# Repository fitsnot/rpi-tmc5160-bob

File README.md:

# rpi-tmc5160-bob
Quick and dirty stepper motor controller based on Raspberry Pi Pico and Trinamic TMC5160-BOB [PCB] [ARDUINO]
The goal is to have either a potentiometer or magentic encoder as rotary input that controls the speed of a large stepper motor. SPI and the integrated motion controller of the Trinamic TMC5160 is used to reduce computational load on the MCU as low as possible.

## Code
The TMC5160_Arduino library by tommag https://github.com/tommag/TMC5160_Arduino is used.

TODO:
- [x] Initial test with RPI and TMC5160-BOB
- [ ] Integrate AS5600 as rotary encoder
- [ ] Tune for utilised MOSFETS

## PCB
FIrst draft uses Raspberry Pi Pico and either a TMC5160-BOB ("Breakout board") or a corresponding SilentStepstick. A AS5600 can be used as a rotary encoder via I2C protocol.

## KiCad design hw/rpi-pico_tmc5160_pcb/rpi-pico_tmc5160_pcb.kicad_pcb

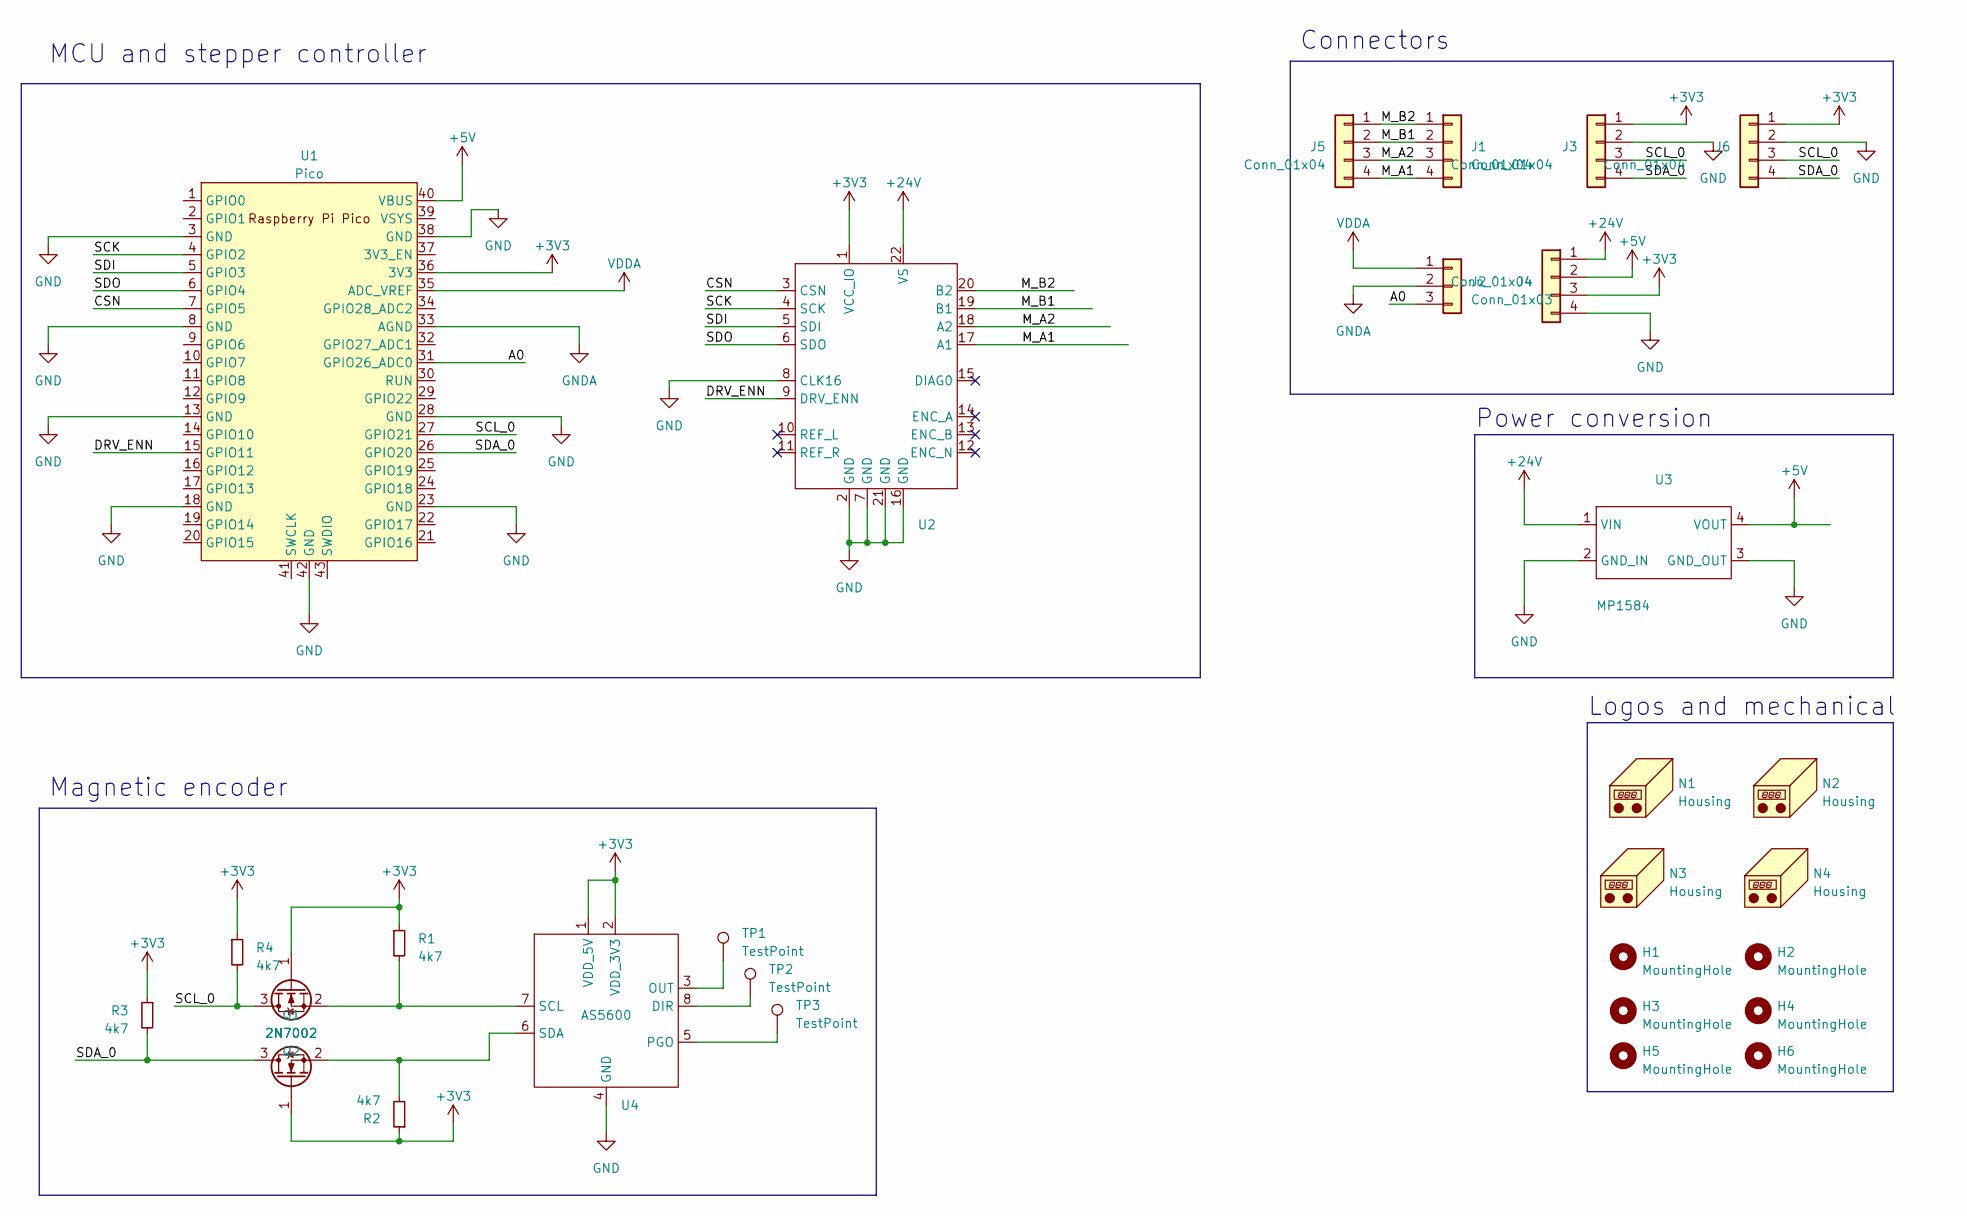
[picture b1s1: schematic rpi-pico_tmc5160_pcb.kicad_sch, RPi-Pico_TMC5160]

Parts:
H1, H2, H3, H4, H5, H6: MountingHole; MountingHole_3.2mm_M3_ISO7380
J1, J4: Conn_01x04; Wago_734-134_1x04_P3.50mm_Vertical; LCSC C557656
J2: Conn_01x03; JST_XH_B3B-XH-A_1x03_P2.50mm_Vertical; LCSC C144394
J3, J5, J6: Conn_01x04; JST_XH_B4B-XH-A_1x04_P2.50mm_Vertical; LCSC C144395
N1, N2, N3, N4: Housing; Mousebite
Q1, Q2: 2N7002; SOT-23; LCSC C8545
R1, R2, R3, R4: 4k7; R_0603_1608Metric_Pad0.98x0.95mm_HandSolder
TP1, TP2, TP3: TestPoint; TestPoint_THTPad_2.0x2.0mm_Drill1.0mm
U1: Pico; RPi_Pico_SMD_TH
U2: TMC5160-BOB
U3: MP1584; MP1584_MOD
U4: AS5600; SOIC-8_3.9x4.9mm_P1.27mm

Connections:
+3V3: J3.1, J4.3, J6.1, Q1.1 (G), Q2.1 (G), R1.1, R2.1, R3.1, R4.1, U1.36 (3V3), U2.1 (VCC_IO), U4.1 (VDD_5V), U4.2 (VDD_3V3)
+5V: J4.2, U1.40 (VBUS), U3.4 (VOUT)
+24V: J4.1, U2.22 (VS), U3.1 (VIN)
/A0: J2.3, U1.31 (GPIO26_ADC0)
/CSN: U1.7 (GPIO5), U2.3 (CSN)
/DRV_ENN: U1.15 (GPIO11), U2.9 (DRV_ENN)
/M_A1: J1.4, J5.4, U2.17 (A1)
/M_A2: J1.3, J5.3, U2.18 (A2)
/M_B1: J1.2, J5.2, U2.19 (B1)
/M_B2: J1.1, J5.1, U2.20 (B2)
/SCK: U1.4 (GPIO2), U2.4 (SCK)
/SCL_0: J3.3, J6.3, Q2.3 (D), R4.2, U1.27 (GPIO21)
/SDA_0: J3.4, J6.4, Q1.3 (D), R3.2, U1.26 (GPIO20)
/SDI: U1.5 (GPIO3), U2.5 (SDI)
/SDO: U1.6 (GPIO4), U2.6 (SDO)
GND: J3.2, J4.4, J6.2, U1.3 (GND), U1.8 (GND), U1.13 (GND), U1.18 (GND), U1.23 (GND), U1.28 (GND), U1.38 (GND), U1.42 (GND), U2.2 (GND), U2.7 (GND), U2.8 (CLK16), U2.16 (GND), U2.21 (GND), U3.2 (GND_IN), U3.3 (GND_OUT), U4.4 (GND)
GNDA: J2.2, U1.33 (AGND)
unnamed: Q1.2 (S), R2.2, U4.6 (SDA)
unnamed: Q2.2 (S), R1.2, U4.7 (SCL)
unnamed: TP2.1, U4.8 (DIR)
unnamed: TP1.1, U4.3 (OUT)
unnamed: TP3.1, U4.5 (PGO)
VDDA: J2.1, U1.35 (ADC_VREF)

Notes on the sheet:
MCU and stepper controller
Connectors
Power conversion
Logos and mechanical
Magnetic encoder

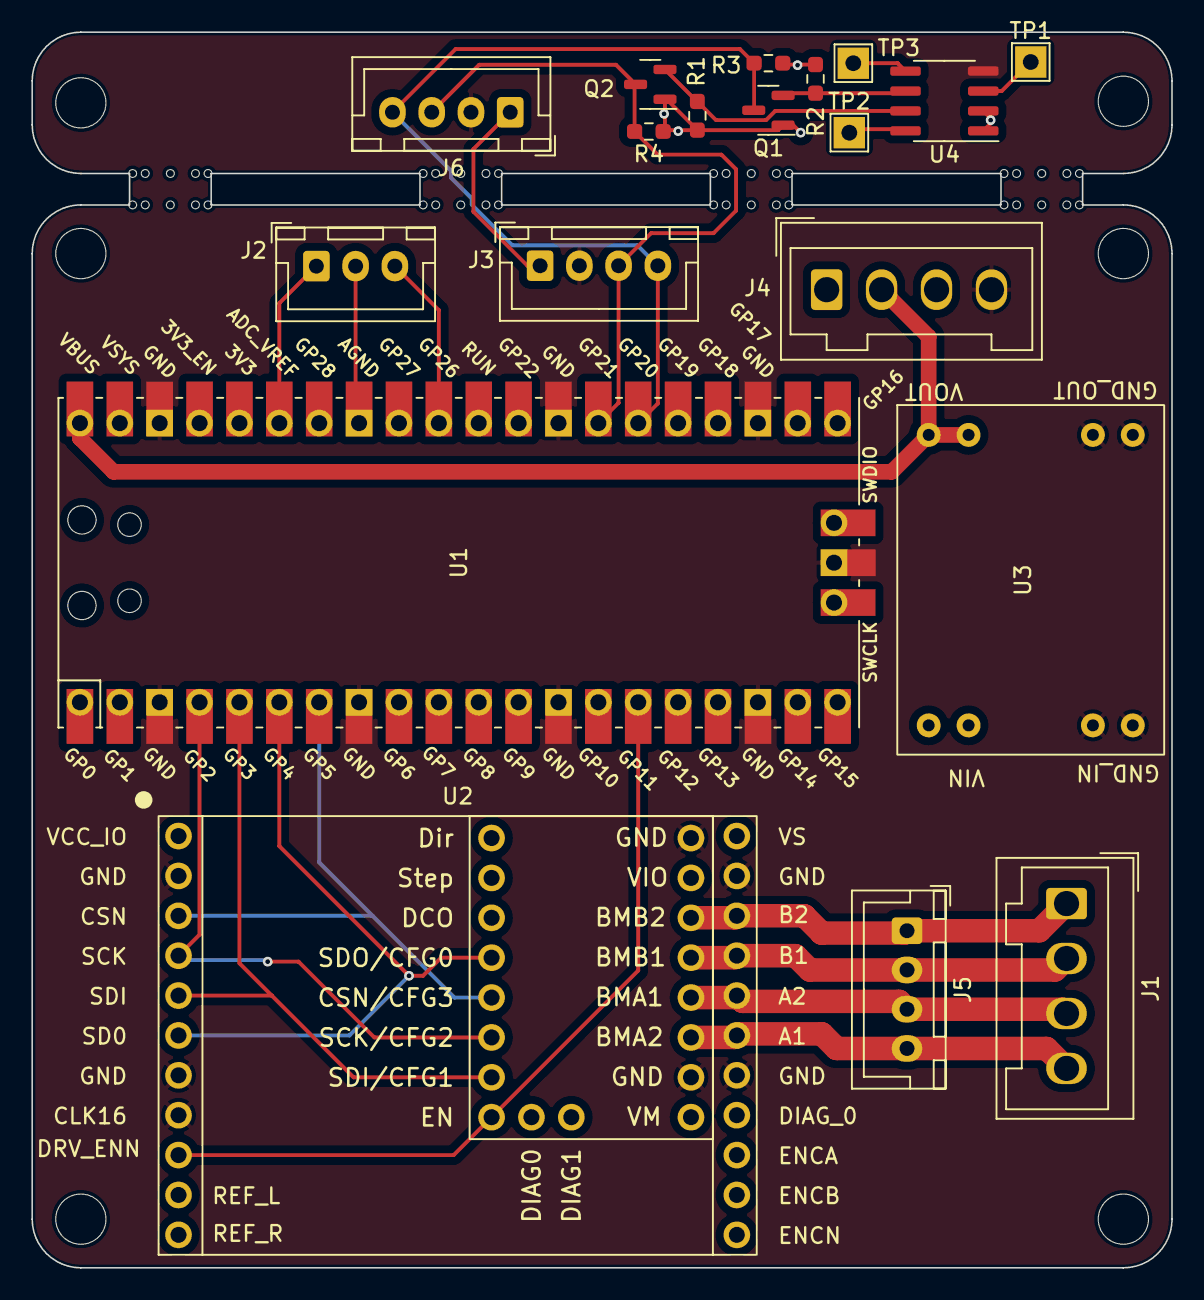
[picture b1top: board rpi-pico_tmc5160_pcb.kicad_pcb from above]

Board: 4 copper layers, 72.6 x 78.7 mm, 29 parts (0 on the bottom side), 23 nets.

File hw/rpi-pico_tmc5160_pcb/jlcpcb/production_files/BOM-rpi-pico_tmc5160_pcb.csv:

Comment,Designator,Footprint,LCSC
Conn_01x03,J2,JST_XH_B3B-XH-A_1x03_P2.50mm_Vertical,C144394
Conn_01x04,"J3,J5,J6",JST_XH_B4B-XH-A_1x04_P2.50mm_Vertical,C144395
4k7,"R1,R2,R3,R4",R_0603_1608Metric_Pad0.98x0.95mm_HandSolder,C23162
AS5600,U4,SOIC-8_3.9x4.9mm_P1.27mm,C499458
Conn_01x04,"J1,J4",Wago_734-134_1x04_P3.50mm_Vertical,C557656
2N7002,"Q1,Q2",SOT-23,C8545
MountingHole,H6,MountingHole_3.2mm_M3_ISO7380,
MountingHole,H5,MountingHole_3.2mm_M3_ISO7380,
MountingHole,H4,MountingHole_3.2mm_M3_ISO7380,
MountingHole,H3,MountingHole_3.2mm_M3_ISO7380,
MountingHole,H2,MountingHole_3.2mm_M3_ISO7380,
MountingHole,H1,MountingHole_3.2mm_M3_ISO7380,
TestPoint,TP3,TestPoint_THTPad_2.0x2.0mm_Drill1.0mm,
MP1584,U3,MP1584_MOD,
Housing,N1,Mousebite,
Housing,N4,Mousebite,
TestPoint,TP1,TestPoint_THTPad_2.0x2.0mm_Drill1.0mm,
~,U2,TMC5160-BOB,
Housing,N2,Mousebite,
Pico,U1,RPi_Pico_SMD_TH,
Housing,N3,Mousebite,
TestPoint,TP2,TestPoint_THTPad_2.0x2.0mm_Drill1.0mm,

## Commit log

2023-06-16 initial comit
2023-06-17 Create LICENSE
2023-06-25 first PCB layout

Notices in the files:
hw/rpi-pico_tmc5160_pcb/rpi-pico_tmc5160_pcb.kicad_sch:
MIT license
